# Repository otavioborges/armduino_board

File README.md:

# ARMduino

ARMduino is an open-source + open-hardware project. Created to be a stepping stone from Arduino development boards to ARM development.

The board feature the same pinout as an Arduino UNO&trade; and same voltage levels on target.

## Board Description

### Power source

The board feature automatic source selection using a LM385 and P-MOSFET (same arrangement as Arduino UNO&trade;). External power range goes from 6~30VDC. Max current supported 0.5A.

### Programmer/Debugger

A MKL26Z32VFM4, using an adapted [DAPLink](https://github.com/mbedmicro/DAPLink) source-code (available on https://bitbucket.org/otavioborges/daplink-if, is used as programmer/debugger through openOCD interface.

### Target

The NXP's MKE02Z64VLD4 replaces the usual ATMEGA8U2 from Arduino. Providing:
 * Enhanced operation frequency (up to 20MHz Bus and core);
 * More flexibility on pin muxing (available on [KE02 Sub-family Data Sheet](http://www.nxp.com/assets/documents/data/en/data-sheets/MKE02P64M20SF0.pdf);
 * SPI, I2C, UART, PWM and ADC peripheral access through break-out connections;
 * I/O signal and periodic interrupts;
 * Debugging capabilities, using MKL26, GDB, DAPLink and openOCD;
 * Up to two breakpoints;
 
### Pinout

The same pin voltage and placement used in Arduino UNO&trade; is available. Furthermore, as NXP MCU provide a range of pin-multiplexing pin-assignment can be altered to fit user's desire.

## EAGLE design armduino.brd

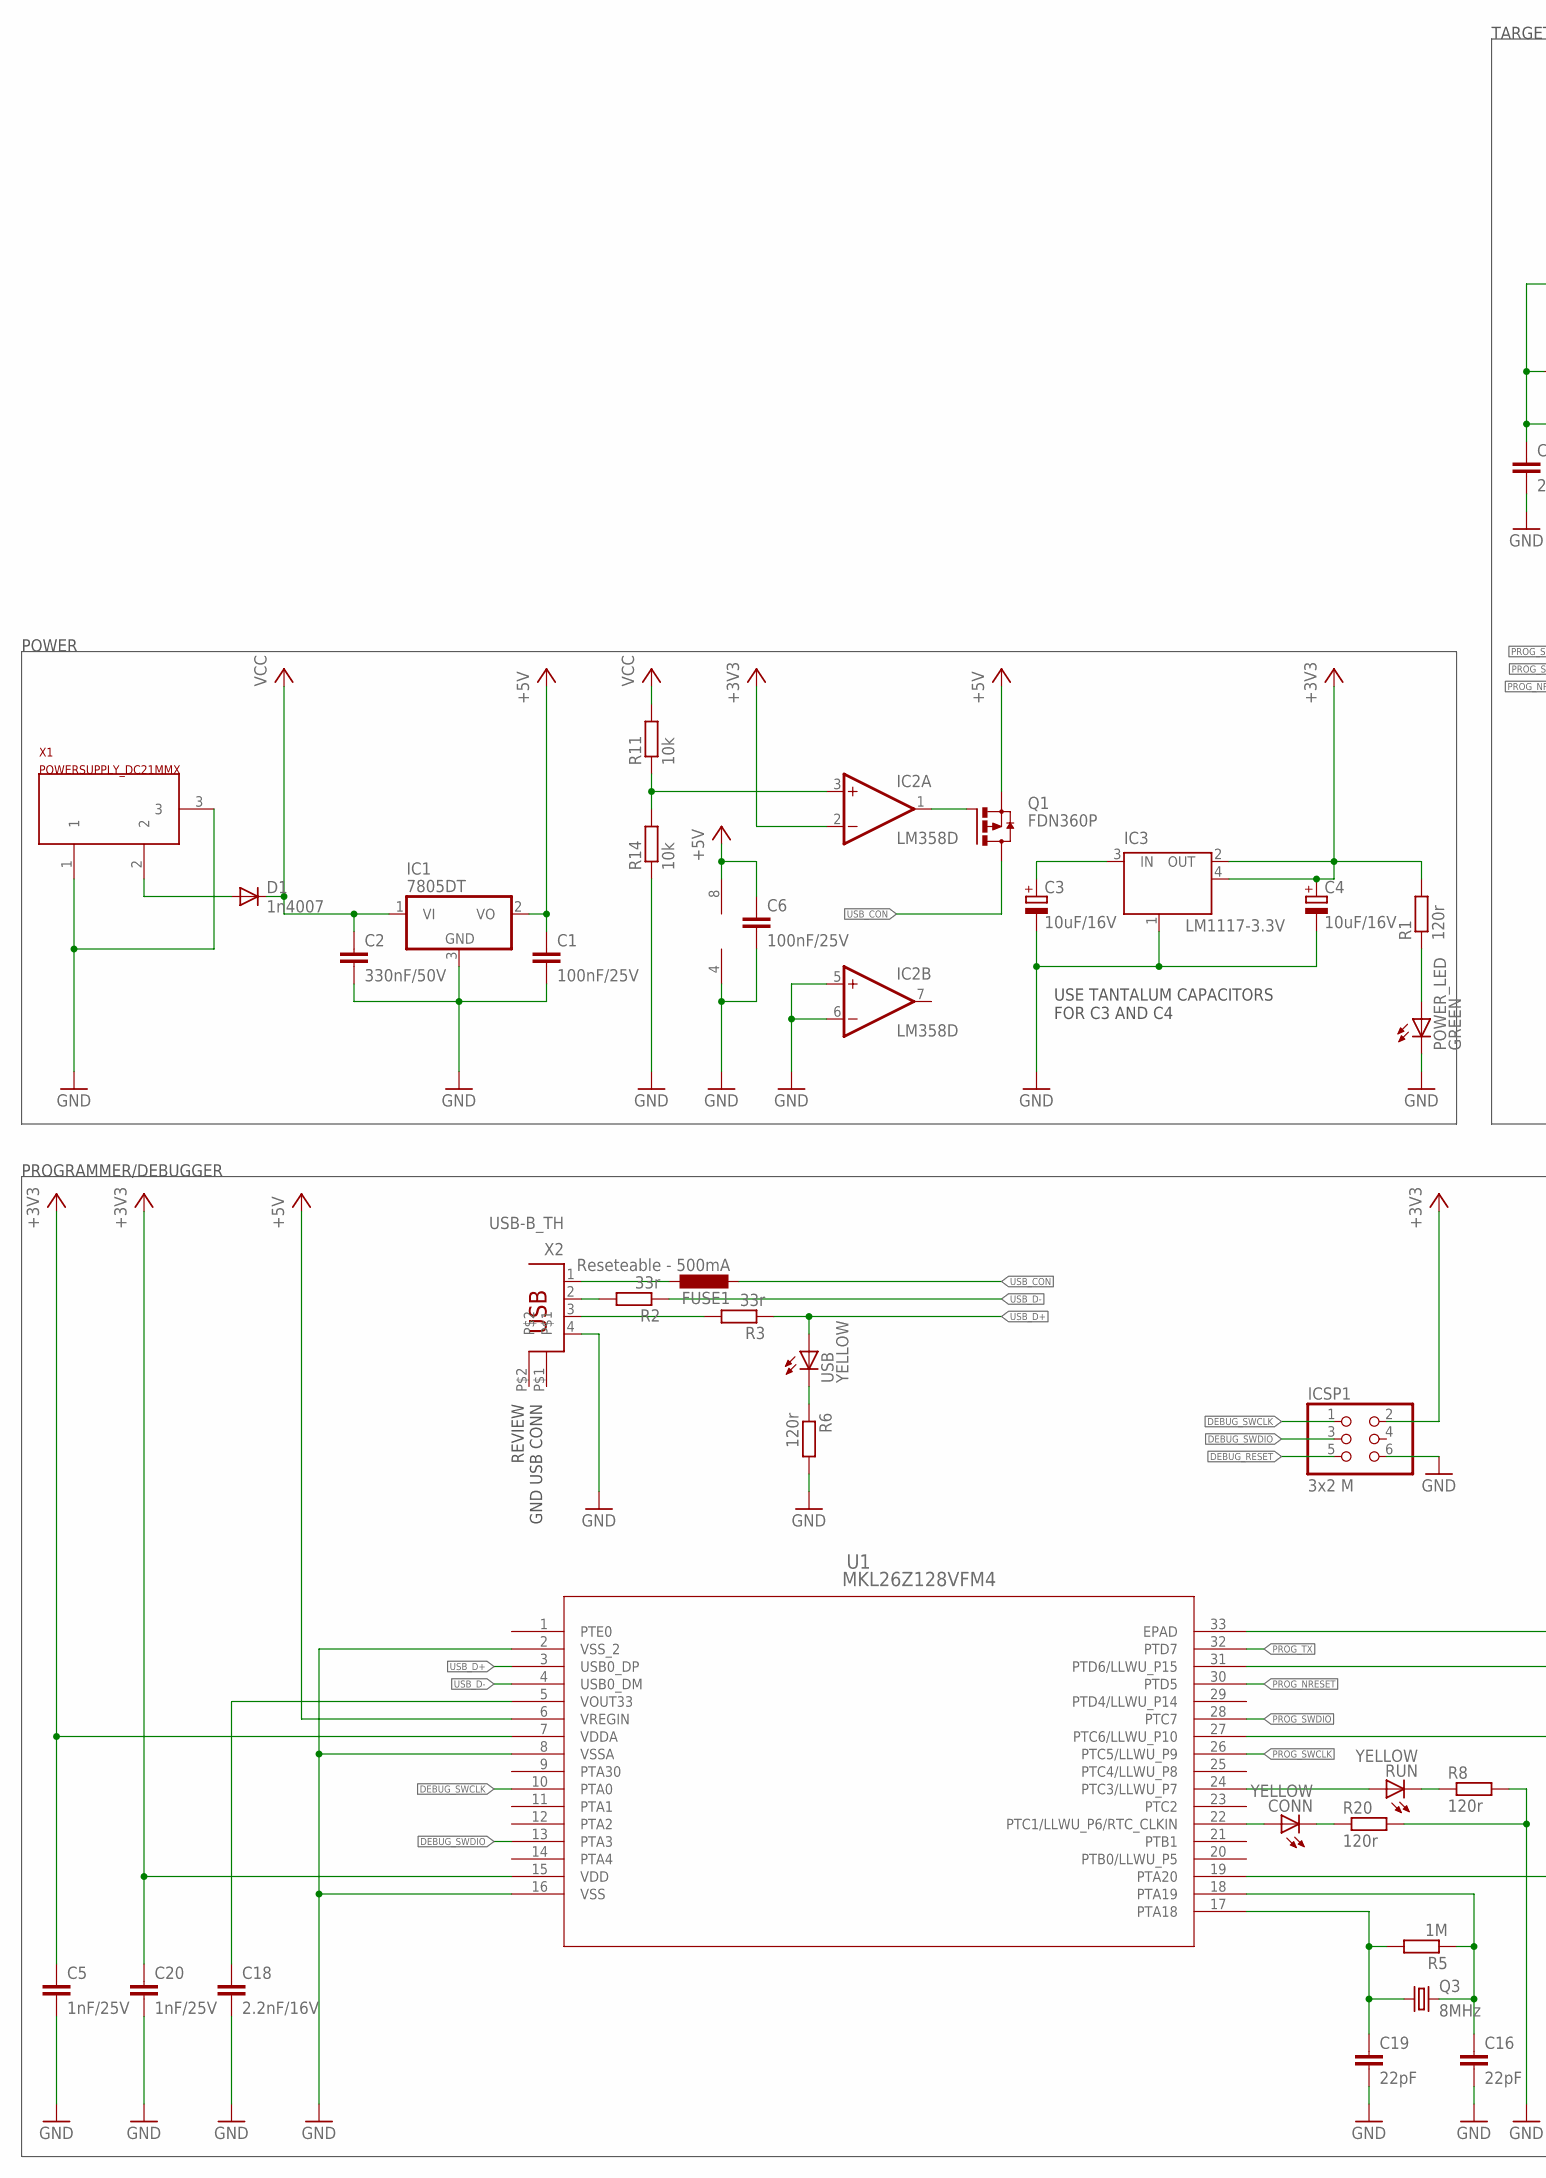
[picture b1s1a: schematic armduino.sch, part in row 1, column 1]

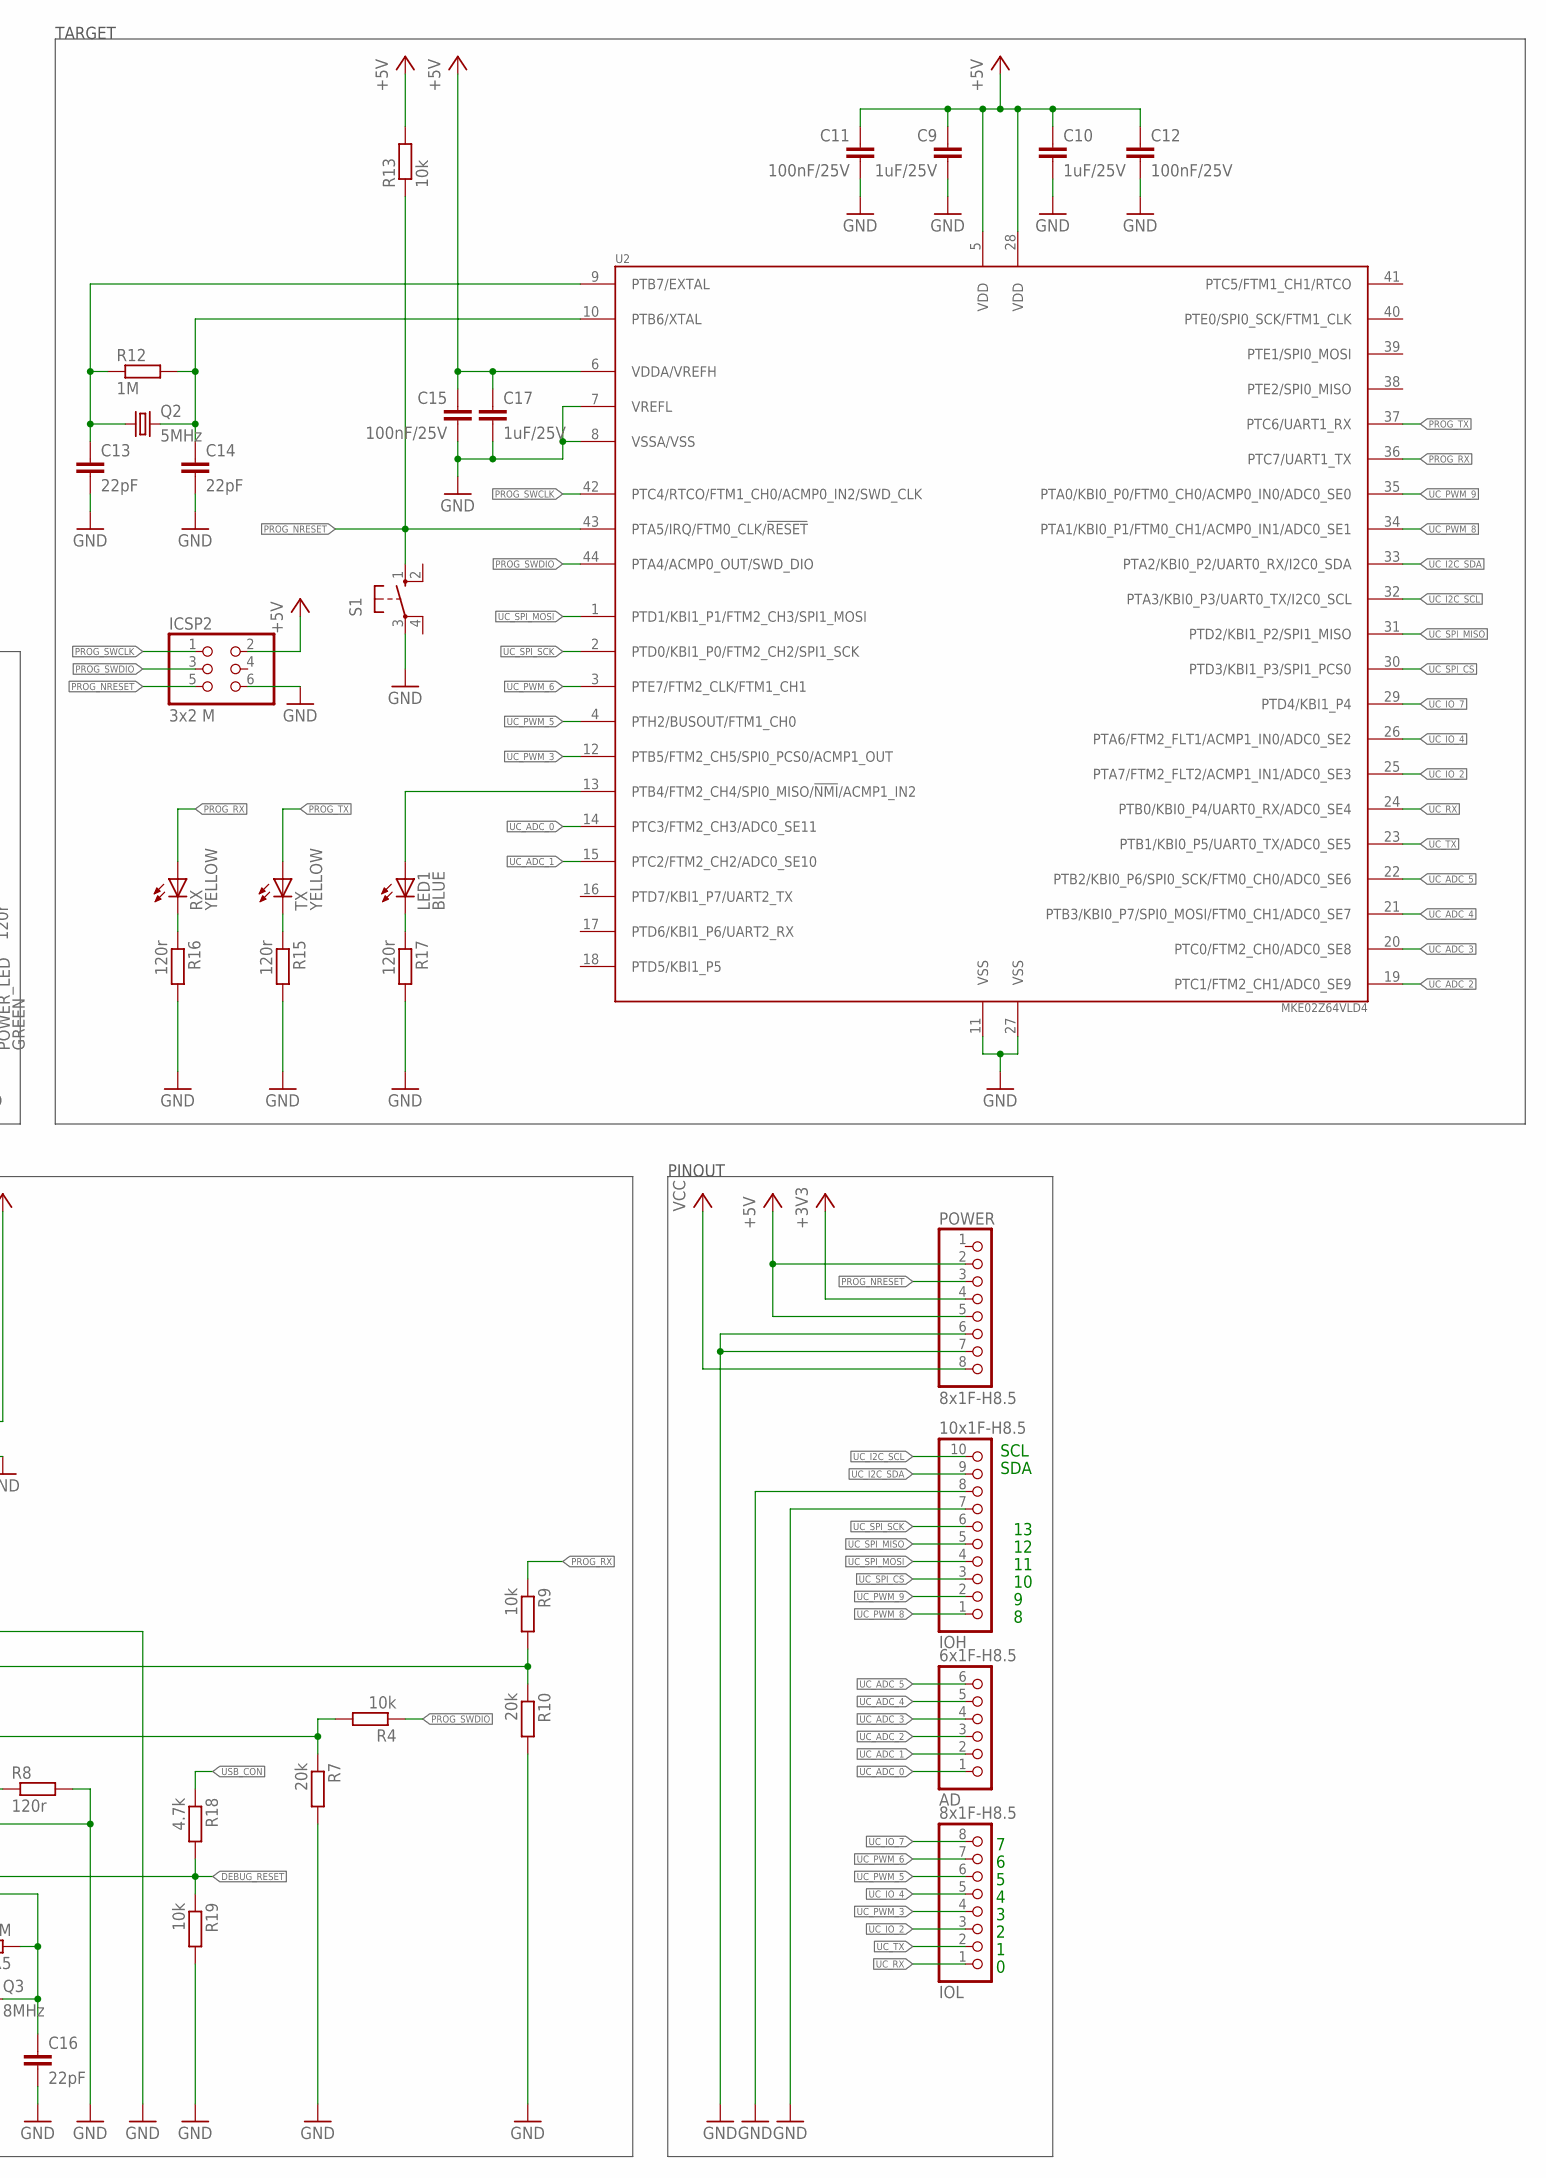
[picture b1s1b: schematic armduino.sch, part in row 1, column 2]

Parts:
AD: 6x1F-H8.5; 1X06
C1, C6, C11, C12, C15: 100nF/25V; C0805K
C2: 330nF/50V; C0805K
C3, C4: 10uF/16V; E2-4
C5, C20: 1nF/25V; C0805K
C9, C10, C17: 1uF/25V; C0805K
C13, C14, C16, C19: 22pF; C0603K
C18: 2.2nF/16V; C0805K
CONN: YELLOW; CHIP-LED0805
D1: 1n4007; DO-214AC
FUSE1: Reseteable - 500mA; L1812
IC1: 7805DT; TO252
IC2: LM358D; SO08
IC3: LM1117-3.3V; SOT223
ICSP1, ICSP2: 3x2 M; 2X03
IOH: 10x1F-H8.5; 1X10
IOL: 8x1F-H8.5; 1X08
LED1: BLUE; CHIP-LED0805
POWER: 8x1F-H8.5; 1X08
POWER_LED: GREEN; CHIP-LED0805
Q1: FDN360P; SUPER-SOT3
Q2: 5MHz; SM49
Q3: 8MHz; HC49/S
R1, R6, R8, R15, R16, R17, R20: 120r; M0805
R2, R3: 33r; M0805
R4, R9, R11, R13, R14, R19: 10k; M0805
R5, R12: 1M; M0805
R7, R10: 20k; M0805
R18: 4.7k; M0805
RUN: YELLOW; CHIP-LED0805
RX: YELLOW; CHIP-LED0805
S1: 10-XX; B3F-10XX
TX: YELLOW; CHIP-LED0805
U1: MKL26Z128VFM4; QFN-32_5X5X0.9
U2: MKE02Z64VLD4; QFP44
USB: YELLOW; CHIP-LED0805
X1: POWERSUPPLY_DC21MMX; POWERSUPPLY_DC-21MM
X2: USB-B_TH; PN61729

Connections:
+3V3: C4.+, C5.1, C20.1, IC2.2 (-IN), IC3.2 (OUT), IC3.4 (OUT), ICSP1.2, POWER.4, R1.2, U1.7 (VDDA), U1.15 (VDD)
+5V: C1.1, C6.1, C9.1, C10.1, C11.1, C12.1, C15.1, C17.1, IC1.2 (VO), IC2.8 (V+), ICSP2.2, POWER.2, POWER.5, Q1.2 (S), R13.2, U1.6 (VREGIN), U2.5 (VDD), U2.6 (VDDA/VREFH), U2.28 (VDD)
CONN: CONN.C, R20.1
DEBUG_RESET: ICSP1.5, R18.2, R19.1, U1.19 (PTA20)
DEBUG_SWCLK: ICSP1.1, U1.10 (PTA0)
DEBUG_SWDIO: ICSP1.3, U1.13 (PTA3)
GND: C1.2, C2.2, C3.-, C4.-, C5.2, C6.2, C9.2, C10.2, C11.2, C12.2, C13.2, C14.2, C15.2, C16.2, C17.2, C18.2, C19.2, C20.2, IC1.3 (GND), IC2.4 (V-), IC2.5 (+IN), IC2.6 (-IN), IC3.1 (GND/ADJ), ICSP1.6, ICSP2.6, IOH.7, IOH.8, POWER.6, POWER.7, POWER_LED.C, R6.2, R7.2, R8.2, R10.2, R14.1, R15.2, R16.2, R17.2, R19.2, R20.2, S1.3, U1.2 (VSS_2), U1.8 (VSSA), U1.16 (VSS), U1.33 (EPAD), U2.7 (VREFL), U2.8 (VSSA/VSS), U2.11 (VSS), U2.27 (VSS), X1.1, X1.3, X2.4
unnamed: D1.A, X1.2
unnamed: POWER_LED.A, R1.1
unnamed: FUSE1.1, X2.1
unnamed: R2.2, X2.2
unnamed: R6.1, USB.C
unnamed: R9.2, R10.1, U1.31 (PTD6/LLWU_P15)
unnamed: R3.2, X2.3
unnamed: R4.2, R7.1, U1.27 (PTC6/LLWU_P10)
unnamed: C3.+, IC3.3 (IN)
unnamed: C18.1, U1.5 (VOUT33)
unnamed: R8.1, RUN.C
unnamed: RUN.A, U1.24 (PTC3/LLWU_P7)
unnamed: CONN.A, U1.22 (PTC1/LLWU_P6/RTC_CLKIN)
unnamed: IC2.3 (+IN), R11.1, R14.2
unnamed: C14.1, Q2.2, R12.2, U2.10 (PTB6/XTAL)
unnamed: C13.1, Q2.1, R12.1, U2.9 (PTB7/EXTAL)
unnamed: R15.1, TX.C
unnamed: R16.1, RX.C
unnamed: LED1.A, U2.13 (PTB4/FTM2_CH4/SPI0_MISO/!NMI!/ACMP1_IN2)
unnamed: LED1.C, R17.1
unnamed: C19.1, Q3.1, R5.2, U1.17 (PTA18)
unnamed: C16.1, Q3.2, R5.1, U1.18 (PTA19)
unnamed: IC2.1 (OUT), Q1.1 (G)
PROG_NRESET: ICSP2.5, POWER.3, R13.1, S1.1 (S), U1.30 (PTD5), U2.43 (PTA5/IRQ/FTM0_CLK/!RESET)
PROG_RX: R9.1, RX.A, U2.36 (PTC7/UART1_TX)
PROG_SWCLK: ICSP2.1, U1.26 (PTC5/LLWU_P9), U2.42 (PTC4/RTCO/FTM1_CH0/ACMP0_IN2/SWD_CLK)
PROG_SWDIO: ICSP2.3, R4.1, U1.28 (PTC7), U2.44 (PTA4/ACMP0_OUT/SWD_DIO)
PROG_TX: TX.A, U1.32 (PTD7), U2.37 (PTC6/UART1_RX)
UC_ADC_0: AD.1, U2.14 (PTC3/FTM2_CH3/ADC0_SE11)
UC_ADC_1: AD.2, U2.15 (PTC2/FTM2_CH2/ADC0_SE10)
UC_ADC_2: AD.3, U2.19 (PTC1/FTM2_CH1/ADC0_SE9)
UC_ADC_3: AD.4, U2.20 (PTC0/FTM2_CH0/ADC0_SE8)
UC_ADC_4: AD.5, U2.21 (PTB3/KBI0_P7/SPI0_MOSI/FTM0_CH1/ADC0_SE7)
UC_ADC_5: AD.6, U2.22 (PTB2/KBI0_P6/SPI0_SCK/FTM0_CH0/ADC0_SE6)
UC_I2C_SCL: IOH.10, U2.32 (PTA3/KBI0_P3/UART0_TX/I2C0_SCL)
UC_I2C_SDA: IOH.9, U2.33 (PTA2/KBI0_P2/UART0_RX/I2C0_SDA)
UC_IO_2: IOL.3, U2.25 (PTA7/FTM2_FLT2/ACMP1_IN1/ADC0_SE3)
UC_IO_4: IOL.5, U2.26 (PTA6/FTM2_FLT1/ACMP1_IN0/ADC0_SE2)
UC_IO_7: IOL.8, U2.29 (PTD4/KBI1_P4)
UC_PWM_3: IOL.4, U2.12 (PTB5/FTM2_CH5/SPI0_PCS0/ACMP1_OUT)
UC_PWM_5: IOL.6, U2.4 (PTH2/BUSOUT/FTM1_CH0)
UC_PWM_6: IOL.7, U2.3 (PTE7/FTM2_CLK/FTM1_CH1)
UC_PWM_8: IOH.1, U2.34 (PTA1/KBI0_P1/FTM0_CH1/ACMP0_IN1/ADC0_SE1)
UC_PWM_9: IOH.2, U2.35 (PTA0/KBI0_P0/FTM0_CH0/ACMP0_IN0/ADC0_SE0)
UC_RX: IOL.1, U2.24 (PTB0/KBI0_P4/UART0_RX/ADC0_SE4)
UC_SPI_CS: IOH.3, U2.30 (PTD3/KBI1_P3/SPI1_PCS0)
UC_SPI_MISO: IOH.5, U2.31 (PTD2/KBI1_P2/SPI1_MISO)
UC_SPI_MOSI: IOH.4, U2.1 (PTD1/KBI1_P1/FTM2_CH3/SPI1_MOSI)
UC_SPI_SCK: IOH.6, U2.2 (PTD0/KBI1_P0/FTM2_CH2/SPI1_SCK)
UC_TX: IOL.2, U2.23 (PTB1/KBI0_P5/UART0_TX/ADC0_SE5)
USB_CON: FUSE1.2, Q1.3 (D), R18.1
USB_D+: R3.1, U1.3 (USB0_DP), USB.A
USB_D-: R2.1, U1.4 (USB0_DM)
VCC: C2.1, D1.C, IC1.1 (VI), POWER.8, R11.2

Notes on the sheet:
SDA
SCL
REVIEW GND USB CONN
USE TANTALUM CAPACITORS FOR C3 AND C4
PROGRAMMER/DEBUGGER
PINOUT
POWER
TARGET

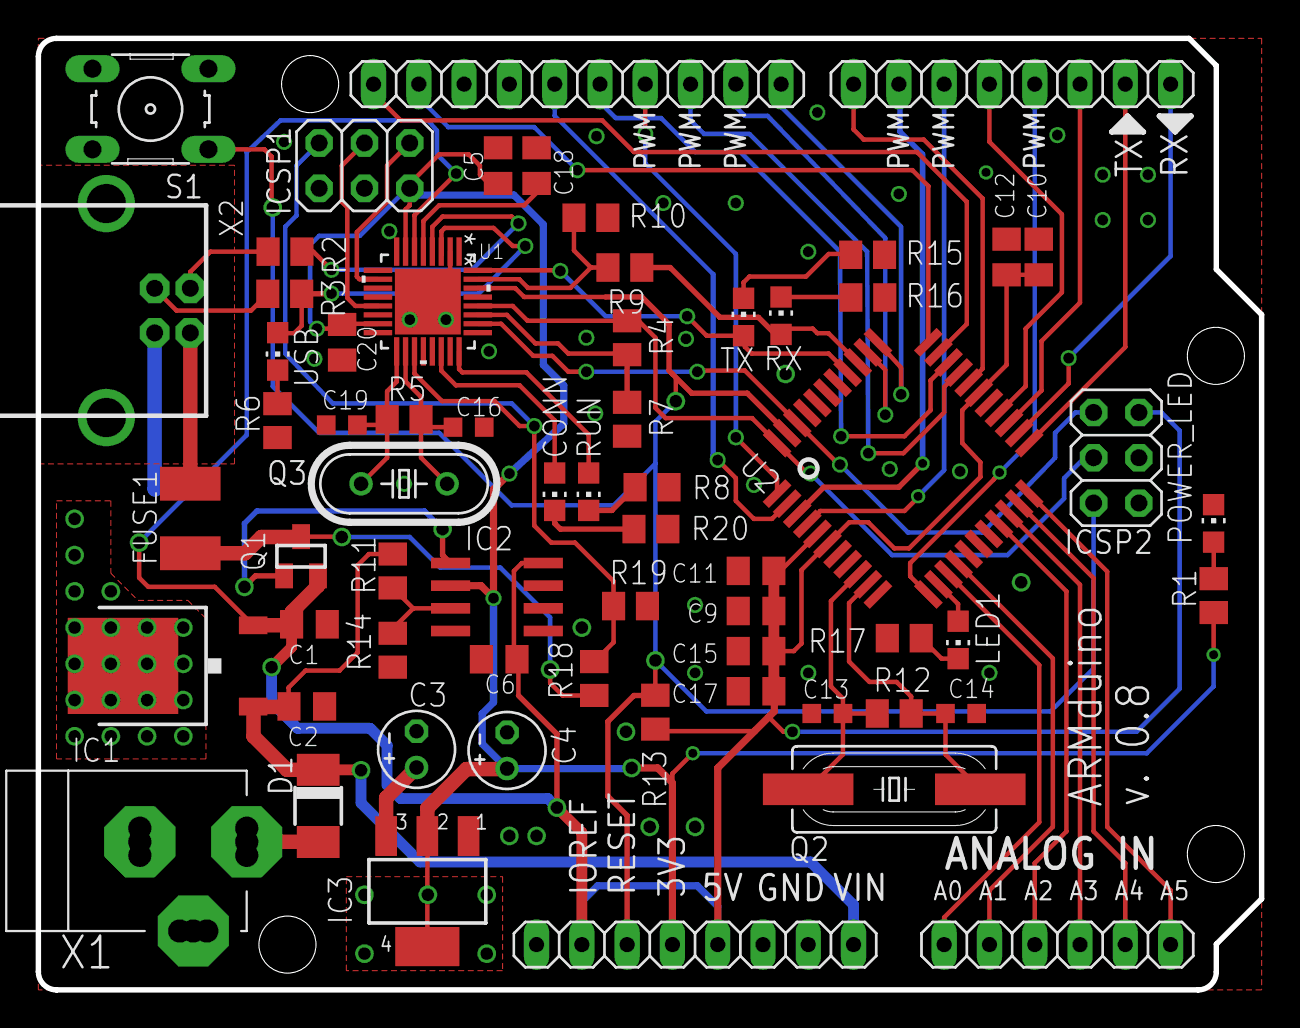
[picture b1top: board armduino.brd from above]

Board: 2 copper layers, 68.6 x 53.4 mm, 64 parts (0 on the bottom side), 61 nets.

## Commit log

2017-04-11 Version 0.2
2017-04-11 Version 0.4
2017-04-11 Removed PWM 3 and 5 from FTM0_FLT pins.
    Some pins were moved around to fit PWM on FTM_CHx pins.
2017-04-11 Correct voltage source selection, correct target XTAL.
    * Add LM358 to switch between external connector and USB source;
    * Target using 20MHz external crystal;
    * Re-route to fit new components;
2017-04-11 Fix version printed on board
2017-04-11 Update README.md
    Corrected links
2017-04-11 Update README.md
    Spelling check
2017-04-16 Modifications to v0.7: * Schematic parts grouped together; * KL26 footprint edited with extended pads, for easier soldering; * SWD signal rerouting to avoid transpositions and unnecessary curves; * A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
2017-04-26 Add led values according to colors to be used and fuse value.
2017-04-26 Fixed target XTAL value, heat dissipation mask, update to version 0.7
2017-04-26 Fixed 100nF caps to same value.
2017-04-26 Add seeed BOM.
2017-05-06 Added dimentions
2017-08-05 Update pad extension over QFN IC
